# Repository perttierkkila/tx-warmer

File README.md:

This project aims to keep RC-flier's hands warm at winter. Nothing prevents
using this product with anything that needs constant heatpower.

### Author
Pertti Erkkilä (pertti.erkkila@gmail.com)

### License
GPLv3

### Story
In Finnish: http://www.kopterit.net/index.php/topic,17572.0.html

### Features
- constant heatpower stages (configurable) using PWM
- lipo-cell count auto-detection
- battery-monitor for cutoff

### Steps to get stuff working
- build hardware
- get Arduino 1.0.1 (1.0.2 won't work)
- get arduino-tiny -libraries (core + PinChangeInterrupt): http://code.google.com/p/arduino-tiny/
- suitable programmer (Arduino as ISP works well)
- for a new chip, burn bootloader
- burn firmware

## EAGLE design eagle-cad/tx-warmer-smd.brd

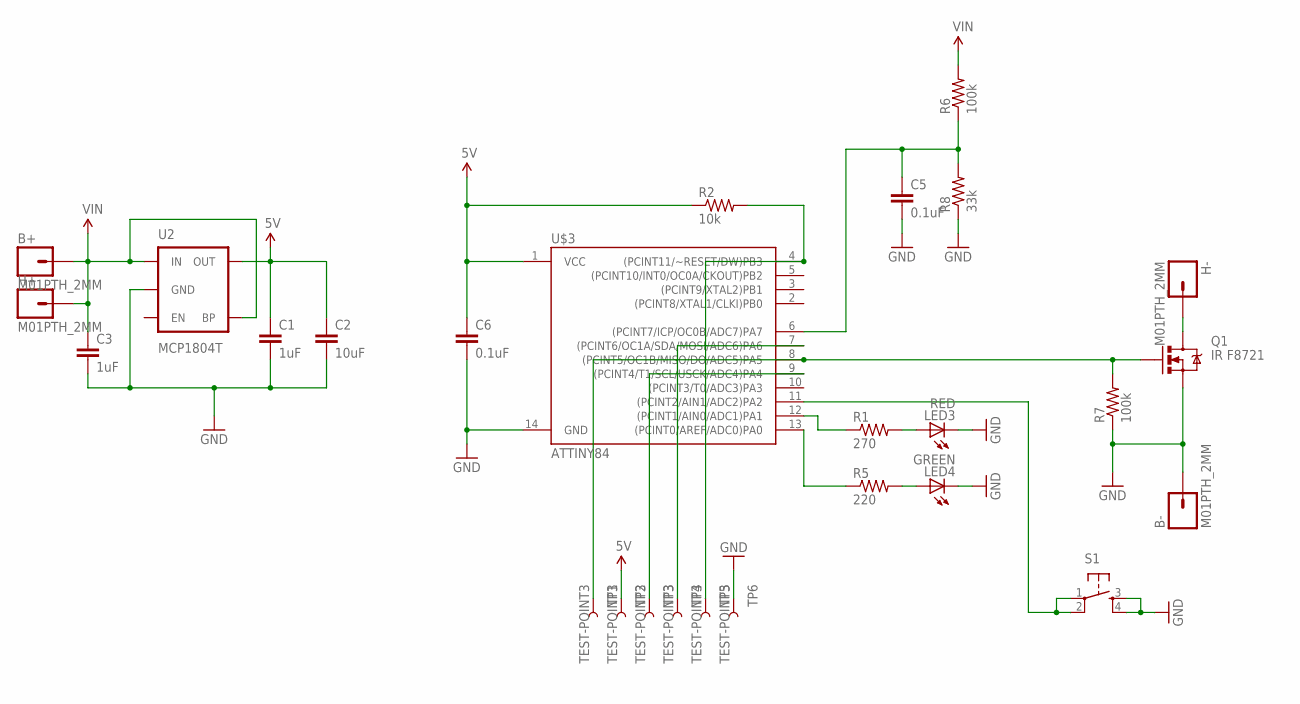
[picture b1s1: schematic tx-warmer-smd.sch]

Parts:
B+: M01PTH_2MM; 1X01_2MM
B-: M01PTH_2MM; 1X01_2MM
C1, C3: 1uF; 0805
C2: 10uF; 0805
C5, C6: 0.1uF; 0805
H+: M01PTH_2MM; 1X01_2MM
H-: M01PTH_2MM; 1X01_2MM
LED3: RED; LED-1206
LED4: GREEN; LED-1206
Q1: IR F8721; SO08
R1: 270; 0805
R2: 10k; 0805
R5: 220; 0805
R6, R7: 100k; 0805
R8: 33k; 0805
S1: TAC_SWITCHSMD; TACTILE_SWITCH_SMD
TP1, TP2, TP3, TP4, TP5, TP6: TEST-POINT3; PAD.03X.03
U2: MCP1804T; SOT23-5
U$3: ATTINY84; SO14

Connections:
5V: C1.1, C2.1, C6.1, R2.1, TP2.P$1, U2.5 (OUT), U$3.1 (VCC)
GND: B-.1, C1.2, C2.2, C3.2, C5.2, C6.2, LED3.C, LED4.C, Q1.1 (S), Q1.2 (S), Q1.3 (S), R7.1, R8.1, S1.3, S1.4, TP6.P$1, U2.2 (GND), U$3.14 (GND)
unnamed: S1.1, S1.2, U$3.11 ((PCINT2/AIN1/ADC2)PA2)
unnamed: C5.1, R6.1, R8.2, U$3.6 ((PCINT7/ICP/OC0B/ADC7)PA7)
unnamed: TP4.P$1, U$3.7 ((PCINT6/OC1A/SDA/MOSI/ADC6)PA6)
unnamed: TP3.P$1, U$3.9 ((PCINT4/T1/SCL/USCK/ADC4)PA4)
unnamed: Q1.4 (G), R7.2, TP1.P$1, U$3.8 ((PCINT5/OC1B/MISO/DO/ADC5)PA5)
unnamed: R1.1, U$3.12 ((PCINT1/AIN0/ADC1)PA1)
unnamed: H-.1, Q1.5 (D), Q1.6 (D), Q1.7 (D), Q1.8 (D)
unnamed: R5.1, U$3.13 ((PCINT0/AREF/ADC0)PA0)
unnamed: R2.2, TP5.P$1, U$3.4 ((PCINT11/~RESET/DW)PB3)
unnamed: LED3.A, R1.2
unnamed: LED4.A, R5.2
VIN: B+.1, C3.1, H+.1, R6.2, U2.1 (IN), U2.4 (BP)

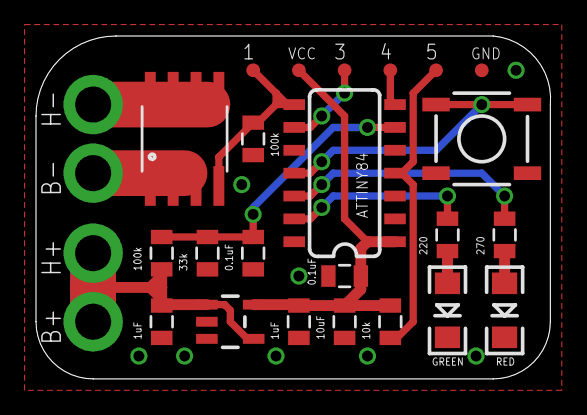
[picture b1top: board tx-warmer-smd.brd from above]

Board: 2 copper layers, 28.6 x 19.0 mm, 27 parts (0 on the bottom side), 14 nets.

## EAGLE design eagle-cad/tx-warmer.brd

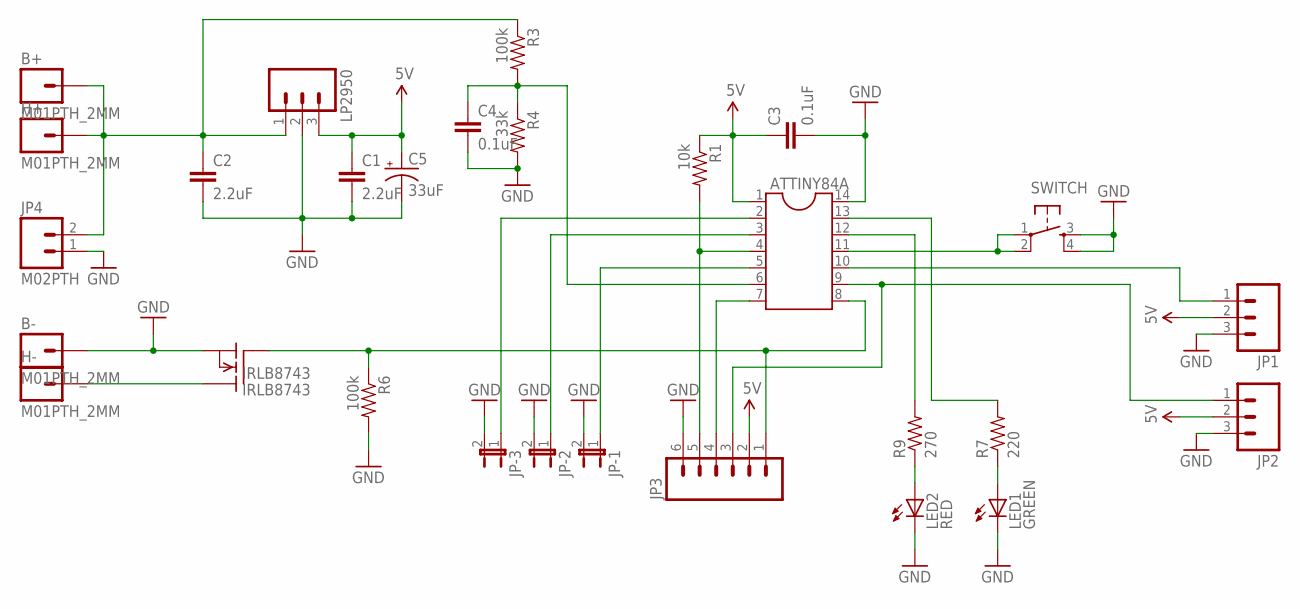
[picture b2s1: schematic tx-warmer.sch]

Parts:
ATTINY84A: DIL14S; SOCKET-14
B+: M01PTH_2MM; 1X01_2MM
B-: M01PTH_2MM; 1X01_2MM
C1, C2: 2.2uF; CAP-PTH-5MM
C3, C4: 0.1uF; CAP-PTH-SMALLEZ
C5: 33uF; CPOL-RADIAL-10UF-25V
H+: M01PTH_2MM; 1X01_2MM
H-: M01PTH_2MM; 1X01_2MM
IRLB8743: IRLB8743; TO220
JP1, JP2: M03PTH; 1X03
JP3: M06SIP; 1X06
JP4: M02PTH; 1X02
JP-1, JP-2, JP-3: JUMPER-2SMD-NO; SJ_2S-NO
LED1: GREEN; LED5MM-KIT
LED2: RED; LED5MM-KIT
LP2950: M031X03_NO_SILK; 1X03_NO_SILK
R1: 10k; AXIAL-0.3EZ
R3, R6: 100k; AXIAL-0.3EZ
R4: 33k; AXIAL-0.3EZ
R7: 220; AXIAL-0.3EZ
R9: 270; AXIAL-0.3EZ
SWITCH: TAC_SWITCHPTH; TACTILE-PTH

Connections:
5V: ATTINY84A.1, C1.1, C3.1, C5.1 (+), JP1.2, JP2.2, JP3.2, LP2950.3, R1.P$1 (1)
GND: ATTINY84A.14, B-.1, C1.2, C2.2, C3.2, C4.2, C5.2 (-), IRLB8743.3 (S), JP1.3, JP2.3, JP3.6, JP4.1, JP-1.2, JP-2.2, JP-3.2, LED1.K (C), LED2.K (C), LP2950.2, R4.P$2 (2), R6.P$2 (2), SWITCH.3, SWITCH.4
unnamed: ATTINY84A.9, JP2.1, JP3.3
unnamed: ATTINY84A.7, JP3.4
unnamed: ATTINY84A.10, JP1.1
unnamed: B+.1, C2.1, H+.1, JP4.2, LP2950.1, R3.P$1 (1)
unnamed: ATTINY84A.5, JP-1.1
unnamed: ATTINY84A.8, IRLB8743.1 (G), JP3.1, R6.P$1 (1)
unnamed: ATTINY84A.6, C4.1, R3.P$2 (2), R4.P$1 (1)
unnamed: LED2.A, R9.P$1 (1)
unnamed: LED1.A, R7.P$1 (1)
unnamed: ATTINY84A.4, JP3.5, R1.P$2 (2)
unnamed: ATTINY84A.12, R9.P$2 (2)
unnamed: ATTINY84A.11, SWITCH.1, SWITCH.2
unnamed: ATTINY84A.13, R7.P$2 (2)
unnamed: H-.1, IRLB8743.2 (D)
unnamed: ATTINY84A.3, JP-2.1
unnamed: ATTINY84A.2, JP-3.1

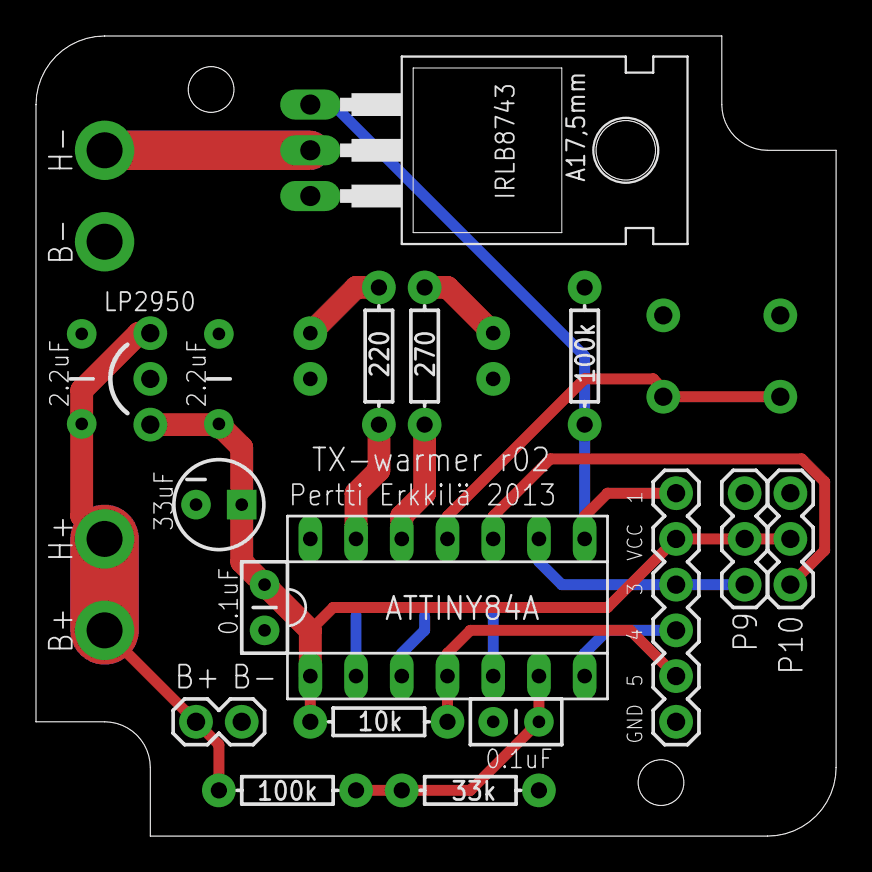
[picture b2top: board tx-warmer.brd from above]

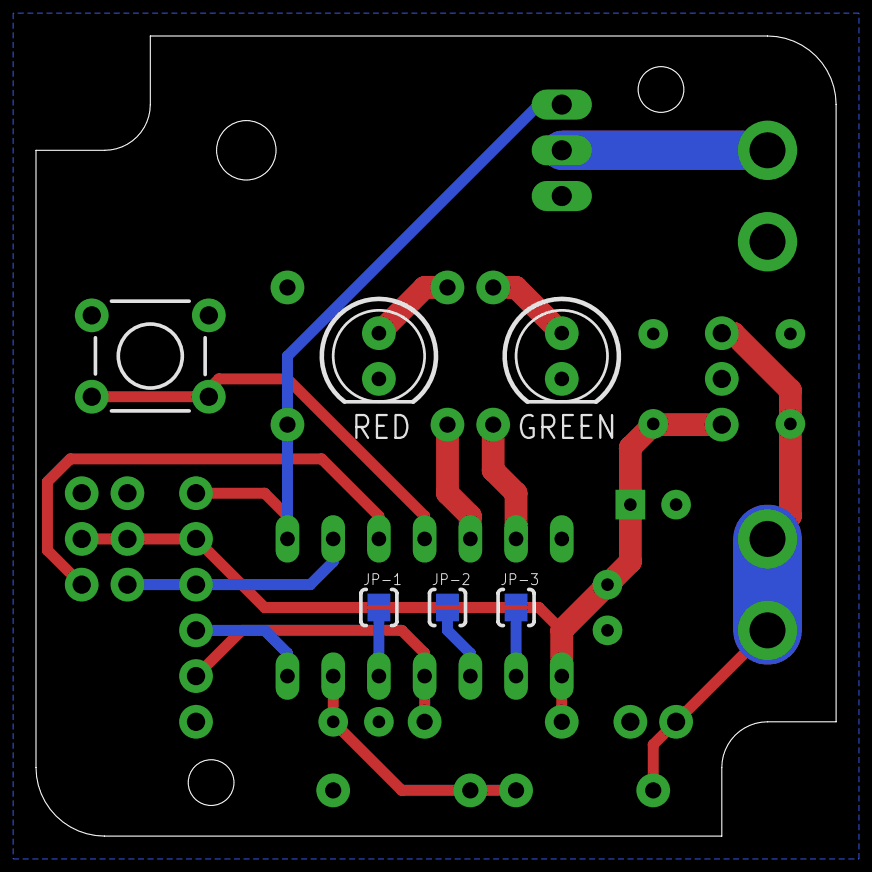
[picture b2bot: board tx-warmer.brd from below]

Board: 2 copper layers, 44.5 x 44.5 mm, 28 parts (6 on the bottom side), 18 nets.

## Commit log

2013-01-06 Eagle CAD schema and board v1.4
2013-01-06 Arduino attiny-firmware
2013-01-06 Removed markdown from README
2013-01-06 Revert "Removed markdown from README"
    This reverts commit 598c8834c325bc921a40a3456d83642b3785a0e2.
2013-01-12 Modified for constant 4S LiFe usage
2013-01-12 Modified for 12v-usage
    Using two hand warmers, each 10.9Ohm and 6 power stages 5->30W.
    Cut-off for 12.5V.
2013-01-14 Tweaked firmware. Lower cell cut-offs and tested prescaler.
2013-01-14 Added steps to get stuff working
2013-01-15 Added description for custom-firmware
2013-01-15 Added description for custom firmware
2013-01-15 Modified critical cut-off
2013-01-15 Changed voltage regulator MCP1702 to LP2950 (formed leads)
2013-01-15 Modified voltage divider to support higher voltages (max now 20.1V)
2013-01-15 Removed ISP-header. Mainly useless and made room for future changes
2013-01-15 Moved PWM from pin5 to pin8
    Reason for this to utilizer timer1 and allows using prescaler without
    interference to delay-methods.
2013-01-15 Added DIP switches and refactored layout
    Switches allow to configure software and reduces firmware variations.
2013-01-16 Minor tweaks to board
2013-01-17 Flipped DIP-switches
2013-01-17 Changed capacitors near regulator from 0.1" to 0.2" spacing
    To avoid confusion with 0.1uF caps and straight legs sit better at board.
2013-01-17 Moved CPU a bit to make room for big cap
    Fixed visibility of new caps.
2013-01-17 Added numbering for DIP switches
    Allows to use jumper wires or 0Ohm resistor instead dip-switches if
    setup is pretty permanent.
2013-01-21 Changed 4P-switch to 6P-switch to utilize all inputs
2013-09-03 SMD-version, r1
2013-09-06 Minor updates to SMD-version
2013-09-06 Added GND-plane to top
2013-09-06 Removed DIP:s, added two sensor ports, bat-pins and prog-interface
2013-09-06 Added SMD-jumpers to empty MC-pins
2013-09-09 Minor fixed to schema/board
2013-09-10 Fixed ldo shutdown-pin and checked values for res/caps
2013-09-14 Added top gnd-plane

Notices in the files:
parts and their libraries:
SparkFun-Capacitors: Licensing: CC v3.0 Share-Alike You are welcome to use this library for commercial purposes.
